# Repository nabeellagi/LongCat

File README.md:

<div align="center">

<!-- Zine -->

---

# Long Cat & FoxCharge

**A custom ESP32-C6 retro game console + fox-themed powerbank, built from scratch.**  
*By Nabeel — 18, Indonesia*

```
   /\_____/\
  /  o   o  \
 ( ==  ^  == )
```

</div>

---

## What Is This?

Long Cat is a handheld retro game console built around a custom ESP32-C6 PCB, put inside a 3D-printed enclosure featuring a long, stoopid cat on the back. It has a 1.3" OLED screen, 5 interface buttons, and a passive buzzer.

FoxCharge is its companion: a fox-themed powerbank with its own custom PCB, and a "Charging Social Battery" label on the back — totally relateable.

---

## Why Does This Exist?
The whole thing exists because I wanted a device where anyone could write their own retro-style game in firmware and actually play it on real hardware! A customizable silly looking project.

---

## How To Use It

### Coding & Flashing

This is the main loop. Open up Arduino IDE, write your game, and flash it to the console over USB-C.

1. Install [Arduino IDE](https://www.arduino.cc/en/software) and add ESP32 board support
2. Plug the console into your PC via USB-C
3. Open or write your game sketch
4. Select the correct board: **ESP32C6 Dev Module**
5. Hit upload, watch it flash, iterate :D

The enclosure pops open magnetically so you never need to unscrew anything to get to the board.

### Playing & Sharing

Once your game is ready and you want to take it somewhere — or just not be tethered to a laptop:

1. Plug the console into the **FoxCharge powerbank** via USB-C
2. The console powers up from the powerbank's 5V output
3. Hand it to a friend. Or play it yourself.

### Modifying the Hardware

Want to tweak the circuit? Change a pin assignment? Add something new? Here's where to go:

- **Console PCB** — open `PCB/board/board.kicad_pro` in [KiCad](https://www.kicad.org/). The schematic, layout, and production files are all in there.
- **FoxCharge PCB** — open `PCB/powerbank/powerbank.epro` in [EasyEDA](https://easyeda.com/). The Interactive BOM HTML (`PCB/powerbank/INTERACTIVE BOM/InteractiveBOM_PCB1_2026-5-30.html`) is very helpful for cross-referencing components on the board visually.

---

## Hardware Overview

### Console

The brain of Long Cat. Designed in KiCad, built around the ESP32-C6.

| Part | What it does |
|---|---|
| **ESP32-C6** | The microcontroller. RISC-V, Wi-Fi 6, BLE 5. Runs your game code. |
| **1.3" OLED** | The screen. I2C, connected on SDA/SCL. This is where everything gets drawn. |
| **5x Buttons** | `BTN_1` through `BTN_5` — your game inputs. Wired to dedicated GPIO pins. |
| **Passive Buzzer** | Makes noise. Driven by a transistor on `BUZZER_PIN`. Louder than what you'd expect!! |
| **Reset / Boot switches** | `SW1` = reset the board, `SW2` = enter bootloader. Useful during development. |
| **Debug header (J1)** | 6-pin header exposing EN, 3V3, TX, GND, RX, BOOT — for serial monitoring or alternate flashing setups. |

### FoxCharge Powerbank

The power source. Custom PCB designed in EasyEDA. Fox-themed. Sleeping fox on the front is load-bearing.

| Part | What it does |
|---|---|
| **Battery** | LiPo 103450 cell (~2000 mAh). |
| **Charge IC — TP4056** | Handles charging the LiPo safely from the USB-C input port. |
| **Boost IC — MT3608** | Steps up the battery voltage (~3.7V) to a stable 5V for the USB-C output. |
| **Protection IC — DW01A + FS8205A** | Protects the battery from overcharge, overdischarge, and short circuits. Keeps things from catching fire. |
| **USB-C Input** | Plug in a charger here to charge the battery. |
| **USB-C Output** | Plug the console here. This is what powers the game. |

---

## Assembly

### Long Cat Console

<p align="center">
  
  <br/>
  
  <br/>
  
</p>

The front and back halves of the enclosure are held together using **6 x 2mm neodymium magnets** on the edges. This means the case snaps shut cleanly and can be pulled apart for flashing or debugging without any tools — which matters a lot when you're iterating on your game code.

To secure the PCB inside the front half: use **M2 screws with nylon M2 nuts**. Nylon nuts ensures the PCB will be locked into the top of the enclosure. Full screw spec is in the BOM (`REAL_BOM/console.csv`).

The Long Cat sticker goes on the back and the Sleepy cat on the front. **This is not optional!!!**.

---

### FoxCharge Powerbank

<p align="center">
  
  <br/>
  
  <br/>
  
  <br/>
  
</p>

Inside the powerbank enclosure, the LiPo battery and PCB are separated using **padded EVA foam** to prevent contact, pressure damage, and general battery unhappiness.

On the inner edges, **Dual Lock Reclosable Fastener (24mm × 50cm Velcro-style)** is used to hold the assembly in place while still allowing it to be opened cleanly for battery replacement or inspection.

Same M2 screw + nylon nut approach as the console for securing the PCB. See `REAL_BOM/powerbank.csv` for the full list.

---

### PCB and Schematics Wiring

<p align="center">
  
  <br/>
  
  <br/>
  
  <br/>
  
  <br/>

</p>

---

## Repository Structure

```
.
├── PCB/
│   ├── board/                          # Console PCB (KiCad)
│   │   ├── board.kicad_pcb
│   │   ├── board.kicad_sch
│   │   ├── board.kicad_pro
│   │   ├── STEP/board.step
│   │   └── production/
│   │       ├── board_gerber.zip        # Send this to your fab
│   │       ├── netlist.ipc
│   │       ├── bom.csv-JLCPCB BOM Tool.xls
│   │       └── raw_bom.csv
│   └── powerbank/                      # FoxCharge PCB (EasyEDA)
│       ├── powerbank.epro
│       ├── powerbank_netlist.tel
│       ├── STEP/
│       ├── GERBER/powerbank_gerber.zip
│       └── INTERACTIVE BOM/
│           ├── BOM_Board1_PCB1_2026-05-30.xlsx
│           └── InteractiveBOM_PCB1_2026-5-30.html
├── enclosure/
│   ├── rawrenders/                     # Reference renders for assembly + zine
│   ├── console/
│   │   ├── enclosure_only.3mf          # Print this
│   │   ├── fullassemblyvisual.3mf      # Full assembly reference
│   │   └── fullassemblyvisual.step
│   └── powerbank/
│       ├── enclosure_only.3mf
│       ├── fullassemblyvisual.3mf
│       └── fullassemblyvisual.step
├── firmware/                           # Hello World for the console
├── stickers/
│   ├── longcat.png
│   ├── sleepcat.png
│   └── tiredfox.png
├── REAL_BOM/
│   ├── all.xlsx
│   ├── console.csv
│   ├── powerbank.csv
│   └── total.csv
└── zine/                               # Full project zine, PDF + PNG versions
```

---

## Stickers

Three stickers are included in `stickers/`. Print them on sticker paper and apply accordingly.

- `longcat.png` — The long, stoopid cat. Goes on the back of the console.
- `sleepcat.png` — Sleeping cat. Goes on the front of the console.
- `tiredfox.png` — The FoxCharge mascot. Goes on the powerbank.

---

## Zine

The `zine/` folder contains both a PDF and PNG version of the project zine, made for Fallout 2026. It's the fastest way to understand what this project is about.

---

## Firmware

An example given inside firmware folder. A simple mechanism to see OLED's output based on button presses. Use it as a starting point for your own games!

---

## OnShape Links
- [Check out the console enclosure](https://cad.onshape.com/documents/60f1f5947965f7d5a461c6ea/w/f31938c96fb582cd81c805fc/e/fdd6c70c168f7e2d293480c5?renderMode=0&uiState=6a1faab33bd1e6d24cdd9844)
- [Check out the powerbank enclosure](https://cad.onshape.com/documents/b2bd0c68b06dcbd9cb3796b5/w/1a262ecd5f3c2cdca41969fa/e/07a6aa8a28141834d2369848?renderMode=0&uiState=6a1faae954f1b396560d079b)

## Bill of Materials

Full BOM is split by subsystem for easier ordering, here are the BOM links:

| File | Contents |
|---|---|
| [`REAL_BOM/console.csv`](https://github.com/nabeellagi/LongCat/blob/main/REAL_BOM/console.csv) | All console PCB components |
| [`REAL_BOM/powerbank.csv`](https://github.com/nabeellagi/LongCat/blob/main/REAL_BOM/powerbank.csv) | All powerbank PCB components |
| [`REAL_BOM/all.xlsx`](https://github.com/nabeellagi/LongCat/blob/main/REAL_BOM/all.xlsx) | Combined, formatted |
| [`REAL_BOM/total.csv`](https://github.com/nabeellagi/LongCat/blob/main/REAL_BOM/total.csv) | Grand total cost summary |

Additional BOM:

1. `PCB/board/production/bom.csv-JLCPCB BOM Tool.xls` is JLCPCB-formatted, ready to upload
2. For the powerbank PCB, the Interactive BOM HTML (`PCB/powerbank/INTERACTIVE BOM/InteractiveBOM_PCB1_2026-5-30.html`) is the friendliest way to cross-reference components with their board placement.

---

### Console BOM

| # | Item | Description | Qty | Unit ($) | Total ($) | Running Total ($) | Link |
|---|---|---|---|---|---|---|---|
| 1 | ESPRESSIF ESP32-C6-WROOM-1-N8 | ESP32 Chip | 1 | 4.3546 | 4.3546 | 4.3546 | [LCSC](https://www.lcsc.com/product-detail/C5366877.html) |
| 2 | TECH PUBLIC TPESD9B3.3ST5G | Diode | 3 | 0.0396 | 0.1188 | 4.4734 | [LCSC](https://www.lcsc.com/product-detail/C2682285.html) |
| 3 | TECH PUBLIC USBLC6-2SC6 | Transient Voltage Suppressor | 1 | 0.0410 | 0.0410 | 4.5144 | [LCSC](https://www.lcsc.com/product-detail/C2827654.html) |
| 4 | BZCN TSC016A04518A | Tactile Switches (console buttons) | 5 | 0.0107 | 0.0535 | 4.5679 | [LCSC](https://www.lcsc.com/product-detail/C2888493.html) |
| 5 | TI LM1117MP-3.3 | Voltage Regulator | 1 | 0.2975 | 0.2975 | 4.8654 | [LCSC](https://www.lcsc.com/product-detail/C3750685.html) |
| 6 | XHXDZ 1207-P6.5MM | Buzzer | 1 | 0.0316 | 0.0316 | 4.8970 | [LCSC](https://www.lcsc.com/product-detail/C49246964.html) |
| 7 | 1N5817W | Diode Schottky | 1 | 0.0197 | 0.0197 | 4.9167 | [LCSC](https://www.lcsc.com/product-detail/C727113.html) |
| 8 | MMBT2222A | Bipolar Transistor | 1 | 0.0155 | 0.0155 | 4.9322 | [LCSC](https://www.lcsc.com/product-detail/C7420351.html) |
| 9 | HS HS13L03W2C01 | 1.3" OLED | 1 | 5.3558 | 5.3558 | 10.2880 | [LCSC](https://www.lcsc.com/product-detail/C7465997.html) |
| 10 | muRata BLM21PG220SN1D | Ferrite Bead | 1 | 0.0308 | 0.0308 | 10.3188 | [LCSC](https://www.lcsc.com/product-detail/C88993.html) |
| 11 | Resistor 1kΩ | R6 | 1 | 0.0011 | 0.0011 | 10.3199 | [LCSC](https://www.lcsc.com/product-detail/C11702.html) |
| 12 | Capacitor 100nF | C2, C5 | 2 | 0.0016 | 0.0032 | 10.3231 | [LCSC](https://www.lcsc.com/product-detail/C1525.html) |
| 13 | Capacitor 1uF | C3, C4 | 2 | 0.0098 | 0.0196 | 10.3427 | [LCSC](https://www.lcsc.com/product-detail/C15849.html) |
| 14 | Korean Hroparts Elec TYPE-C-31-M-12 | USB-C Input | 1 | 0.1725 | 0.1725 | 10.5152 | [LCSC](https://www.lcsc.com/product-detail/C165948.html) |
| 15 | Capacitor 10uF | C1 | 1 | 0.2500 | 0.2500 | 10.7652 | [LCSC](https://www.lcsc.com/product-detail/C19702.html) |
| 16 | B3U-1000P | ESP32 Buttons | 3 | 0.1781 | 0.5343 | 11.2995 | [LCSC](https://www.lcsc.com/product-detail/C231329.html) |
| 17 | Resistor 2.2kΩ | R7, R8 | 2 | 0.0008 | 0.0008 | 11.3003 | [LCSC](https://www.lcsc.com/product-detail/C25879.html) |
| 18 | Resistor 5.1kΩ | R4, R5 | 2 | 0.0009 | 0.0018 | 11.3021 | [LCSC](https://www.lcsc.com/product-detail/C25905.html) |
| 19 | Capacitor 22uF | C6, C7 | 2 | 0.0618 | 0.1236 | 11.4257 | [LCSC](https://www.lcsc.com/product-detail/C45783.html) |
| 20 | R+O SMD1206-050-30 | Reset Fuse | 1 | 0.0599 | 0.0599 | 11.4856 | [LCSC](https://www.lcsc.com/product-detail/C46641016.html) |
| 21 | ZHOURI 2.54-2*3 | Pin Header | 1 | 0.0562 | 0.0562 | 11.5418 | [LCSC](https://www.lcsc.com/product-detail/C5116479.html) |
| 22 | Resistor 10kΩ | R1, R2, R3 | 3 | 0.0009 | 0.0027 | 11.5445 | [LCSC](https://www.lcsc.com/product-detail/C60490.html) |
| 23 | 6×2mm Strong Magnet Neodymium | Enclosure attach/detach | 6 | 0.0530 | 0.3180 | 11.8625 | [Tokopedia](https://tk.tokopedia.com/ZSxcDM12f/) |
| 24 | M2×8 Screw | Screw PCB to enclosure | 4 | 0.0500 | 0.2000 | 12.0625 | [Tokopedia](https://tk.tokopedia.com/ZSxcDKrx9/) |
| 25 | M2 Nylon Nut | Lock the screw | 4 | 0.0540 | 0.2160 | 12.2785 | [Tokopedia](https://tk.tokopedia.com/ZSxcP4PVw/) |
| 26 | Engineering Fee | Engineering Fee | 1 | 24.0000 | 24.0000 | 36.2785 | [JLCPCB](https://jlcpcb.com/) |
| 27 | PCB Board | PCB Board | 1 | 1.6000 | 1.6000 | 37.8785 | [JLCPCB](https://jlcpcb.com/) |
| 28 | PCBA Price | If enabled PCBA option | 1 | 42.1700 | 42.1700 | 80.0485 | [JLCPCB](https://jlcpcb.com/) |

> **Console subtotal (without PCBA): $37.88** — components + engineering fee + PCB board  
> **Console subtotal (with PCBA): $80.05** — includes assembly service

---

### FoxCharge Powerbank BOM

| # | Item | Description | Qty | Unit ($) | Total ($) | Running Total ($) | Link |
|---|---|---|---|---|---|---|---|
| 1 | TPOWER TP4056 | Charging Module | 1 | 0.1194 | 0.1194 | 0.1194 | [LCSC](https://www.lcsc.com/product-detail/C382139.html) |
| 2 | PUOLOP DW01A | Battery Protection (overcharge prevention) | 1 | 0.0428 | 0.0428 | 0.1622 | [LCSC](https://www.lcsc.com/product-detail/C351410.html) |
| 3 | XI'AN Aerosemi Tech MT3608 | Boost Step-Up Regulator | 1 | 0.0786 | 0.0786 | 0.2408 | [LCSC](https://www.lcsc.com/product-detail/C84817.html) |
| 4 | TECH PUBLIC FS8205A | LiPo Battery Protection FET | 1 | 0.0575 | 0.0575 | 0.2983 | [LCSC](https://www.lcsc.com/product-detail/C2830320.html) |
| 5 | SHOU HAN TYPE-C 16PIN 2MD(073) | USB-C Input and Output | 2 | 0.0742 | 0.1484 | 0.4467 | [LCSC](https://www.lcsc.com/product-detail/C2765186.html) |
| 6 | Hubei KENTO Elec KT-0603R | Red LED | 1 | 0.0070 | 0.0070 | 0.4537 | [LCSC](https://www.lcsc.com/product-detail/C2286.html) |
| 7 | Hubei KENTO Elec KT-0805G | Green LED | 1 | 0.0163 | 0.0163 | 0.4700 | [LCSC](https://www.lcsc.com/product-detail/C2297.html) |
| 8 | EVERLIGHT 19-213/BHC-ZL1M2RY/5T | Blue LED | 1 | 0.0381 | 0.0381 | 0.5081 | [LCSC](https://www.lcsc.com/product-detail/C2987539.html) |
| 9 | cjiang FXL0420-4R7-M | Inductor 4.7µH | 1 | 0.2076 | 0.2076 | 0.7157 | [LCSC](https://www.lcsc.com/product-detail/C167208.html) |
| 10 | JST S2B-PH-SM4-TB(LF)(SN) | JST Pin for Battery | 1 | 0.2040 | 0.2040 | 0.9197 | [LCSC](https://www.lcsc.com/product-detail/C295747.html) |
| 11 | LiPo 104050 2000mAh 3.7V | Battery | 1 | 4.8300 | 4.8300 | 5.7497 | [Tokopedia](https://tk.tokopedia.com/ZSxtYCQTL/) |
| 12 | Resistor 5.1kΩ | R1, R2 | 2 | 0.0003 | 0.0006 | 5.7503 | [LCSC](https://www.lcsc.com/product-detail/C23186.html) |
| 13 | Resistor 470Ω | R3, R4 | 2 | 0.0003 | 0.0006 | 5.7509 | [LCSC](https://www.lcsc.com/product-detail/C23179.html) |
| 14 | Resistor 10kΩ | R5 | 1 | 0.0003 | 0.0003 | 5.7512 | [LCSC](https://www.lcsc.com/product-detail/C25804.html) |
| 15 | Resistor 1.2kΩ | R6 | 1 | 0.0003 | 0.0003 | 5.7515 | [LCSC](https://www.lcsc.com/product-detail/C114605.html) |
| 16 | Resistor 1kΩ | R7, R12 | 2 | 0.0003 | 0.0006 | 5.7521 | [LCSC](https://www.lcsc.com/product-detail/C22548.html) |
| 17 | Resistor 110kΩ | R8 | 1 | 0.0002 | 0.0002 | 5.7523 | [LCSC](https://www.lcsc.com/product-detail/C25805.html) |
| 18 | Resistor 15kΩ | R9 | 1 | 0.0003 | 0.0003 | 5.7526 | [LCSC](https://www.lcsc.com/product-detail/C114661.html) |
| 19 | Resistor 56kΩ | R10, R11 | 2 | 0.0003 | 0.0006 | 5.7532 | [LCSC](https://www.lcsc.com/product-detail/C23206.html) |
| 20 | Resistor 100Ω | R13 | 1 | 0.0003 | 0.0003 | 5.7535 | [LCSC](https://www.lcsc.com/product-detail/C105588.html) |
| 21 | Capacitor 10uF | C1, C2 | 2 | 0.0019 | 0.0038 | 5.7573 | [LCSC](https://www.lcsc.com/product-detail/C19702.html) |
| 22 | Capacitor 22uF | C3, C4 | 2 | 0.0027 | 0.0054 | 5.7627 | [LCSC](https://www.lcsc.com/product-detail/C86295.html) |
| 23 | Capacitor 100nF | C6 | 1 | 0.0003 | 0.0003 | 5.7630 | [LCSC](https://www.lcsc.com/product-detail/C160831.html) |
| 24 | 3M Dual Lock Fastener 24mm×50cm | Enclosure attach/detach (use 3mm×3mm pieces) | 6 | 0.0010 | 0.0060 | 5.7690 | [Tokopedia](https://tk.tokopedia.com/ZSxcDnUcT/) |
| 25 | M2×8 Screw | Screw PCB to enclosure | 4 | 0.0500 | 0.2000 | 5.9690 | [Tokopedia](https://tk.tokopedia.com/ZSxcDKrx9/) |
| 26 | M2 Nylon Nut | Lock the screw | 4 | 0.0540 | 0.2160 | 6.1850 | [Tokopedia](https://tk.tokopedia.com/ZSxc5xuDv/) |
| 27 | PCB Board | PCB Board | 1 | 1.0000 | 1.0000 | 7.1850 | [JLCPCB](https://jlcpcb.com/) |
| 28 | PCBA Price | If enabled PCBA option | 1 | 70.2500 | 70.2500 | 77.4350 | [JLCPCB](https://jlcpcb.com/) |

> **Powerbank subtotal (without PCBA): $7.19** — components + PCB board  
> **Powerbank subtotal (with PCBA): $77.44** — includes assembly service

---

### Grand Total

| Scenario | Console | Powerbank | **Total** |
|---|---|---|---|
| **Without PCBA** (self-solder) | $37.88 | $7.19 | **$45.06** |
| **With PCBA** (JLCPCB assembles) | $80.05 | $77.44 | **$157.48** |

> PCBA (PCB Assembly) is the option where JLCPCB solders all SMD components onto the board for you.

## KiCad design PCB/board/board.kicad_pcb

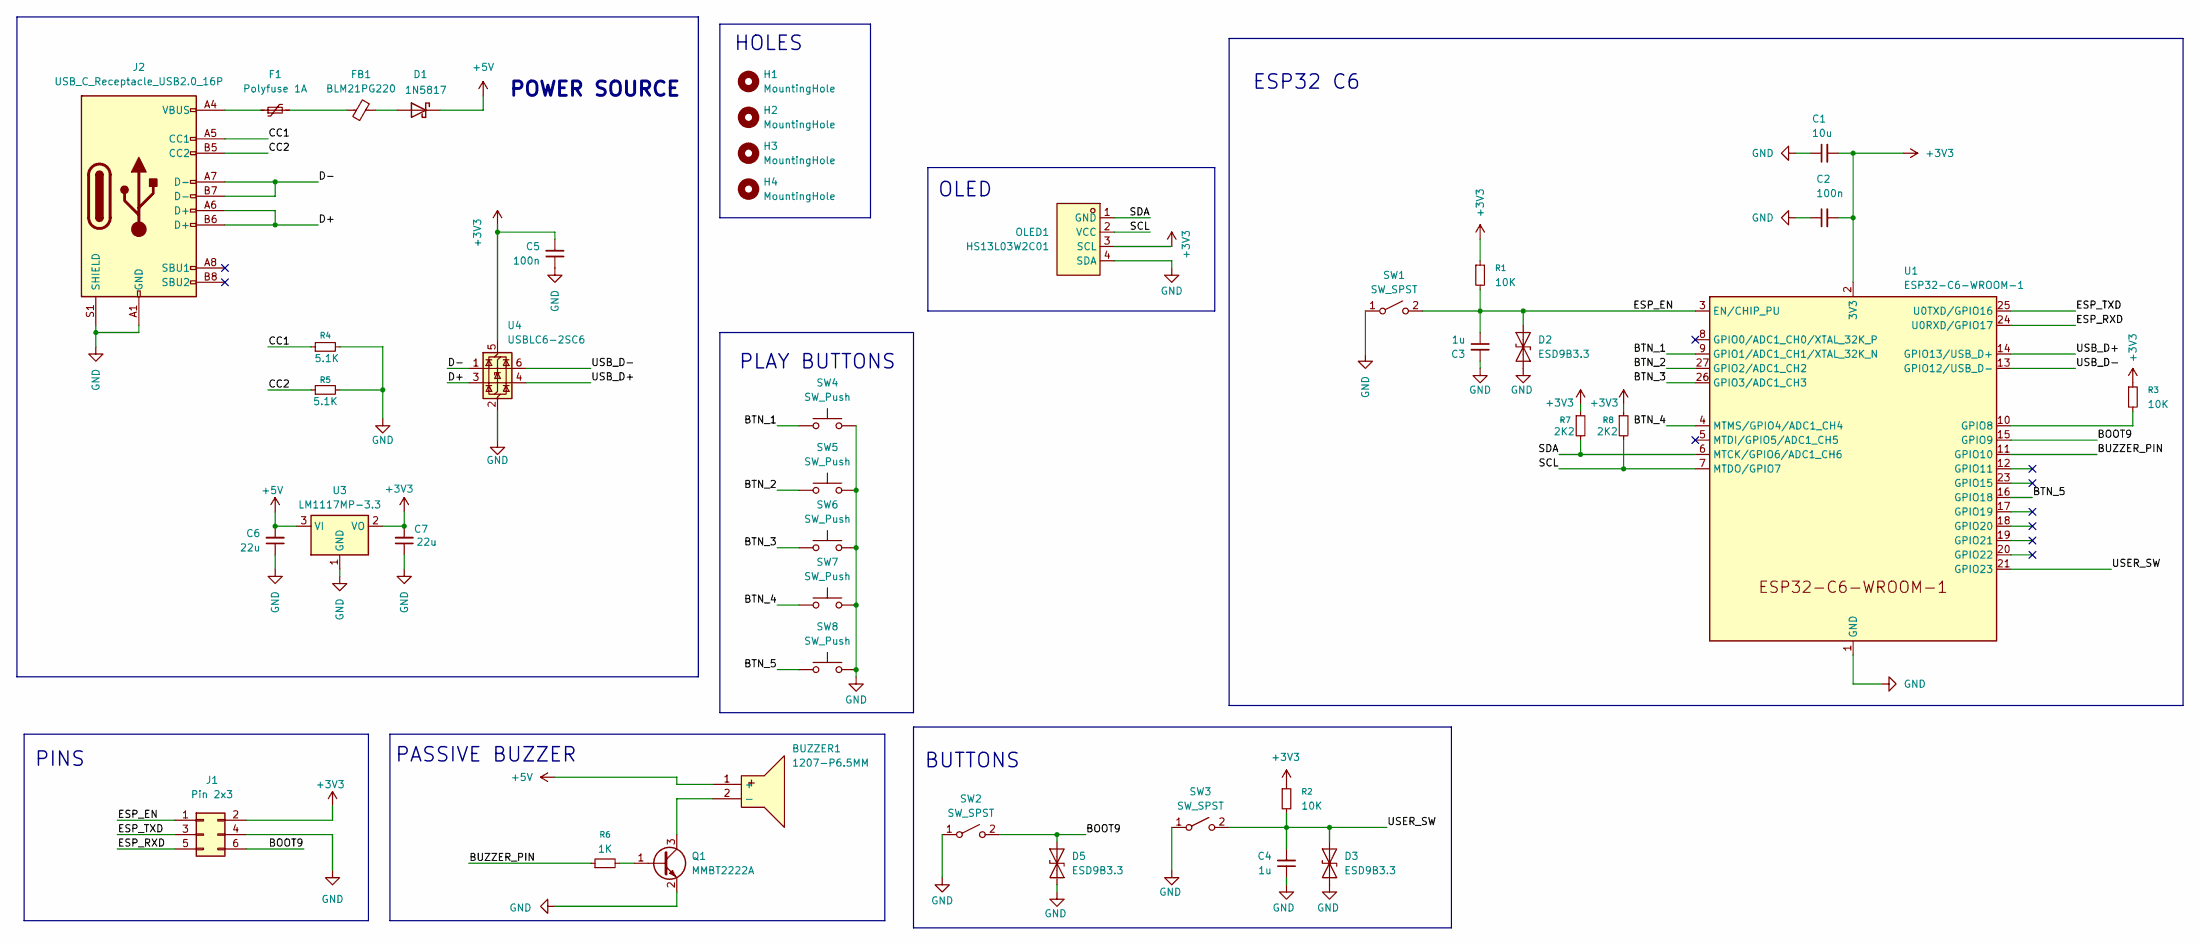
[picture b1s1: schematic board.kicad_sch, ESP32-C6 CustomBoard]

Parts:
BUZZER1: 1207-P6.5MM; BUZ-TH_BD12.5-P6.50-D1.4; MPN 1207-P6.5MM; LCSC Part C49246964
C1: 10u; C_0603_1608Metric
C2, C5: 100n; C_0402_1005Metric
C3, C4: 1u; C_0603_1608Metric
C6, C7: 22u; C_0805_2012Metric
D1: 1N5817; D_SOD-123
D2, D3, D5: ESD9B3.3; D_SOD-923
F1: Polyfuse 1A; Fuse_1206_3216Metric
FB1: BLM21PG220; L_0805_2012Metric
H1, H2, H3, H4: MountingHole; MountingHole_2.2mm_M2_DIN965_Pad
J1: Pin 2x3; PinSocket_2x03_P2.54mm_Vertical
J2: USB_C_Receptacle_USB2.0_16P; USB_C_Receptacle_HRO_TYPE-C-31-M-12
OLED1: HS13L03W2C01; OLED-TH_L35.4-W33.5_HS13L03W2C01; MPN HS13L03W2C01; LCSC Part C7465997
Q1: MMBT2222A; SOT-23
R1, R2, R3: 10K; R_0402_1005Metric
R4, R5: 5.1K; R_0402_1005Metric
R6: 1K; R_0402_1005Metric
R7, R8: 2K2; R_0402_1005Metric
SW1, SW2, SW3: SW_SPST; SW_SPST_B3U-1000P
SW4, SW5, SW6, SW7, SW8: SW_Push; SW-TH_4P-L4.5-W4.5-P3.00-LS4.8
U1: ESP32-C6-WROOM-1
U3: LM1117MP-3.3; SOT-223-3_TabPin2
U4: USBLC6-2SC6; SOT-23-6

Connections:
+3V3: C1.2, C2.2, C5.2, C7.2, J1.2, OLED1.3 (SCL), R1.1, R2.1, R3.1, R7.1, R8.1, U1.2 (3V3), U3.2 (VO), U4.5 (VBUS)
+5V: BUZZER1.1 (+), C6.2, D1.1 (K), U3.3 (VI)
/BOOT9: D5.2 (A2), J1.6, SW2.2 (B), U1.15 (GPIO9)
/BTN_1: SW4.2, U1.9 (GPIO1/ADC1_CH1/XTAL_32K_N)
/BTN_2: SW5.2, U1.27 (GPIO2/ADC1_CH2)
/BTN_3: SW6.2, U1.26 (GPIO3/ADC1_CH3)
/BTN_4: SW7.2, U1.4 (MTMS/GPIO4/ADC1_CH4)
/BTN_5: SW8.2, U1.16 (GPIO18)
/BUZZER_PIN: R6.1, U1.11 (GPIO10)
/CC1: J2.A5 (CC1), R4.1
/CC2: J2.B5 (CC2), R5.1
/D+: J2.A6 (D+), J2.B6 (D+), U4.3 (I/O2)
/D-: J2.A7 (D-), J2.B7 (D-), U4.1 (I/O1)
/ESP_EN: C3.1, D2.2 (A2), J1.1, R1.2, SW1.2 (B), U1.3 (EN/CHIP_PU)
/ESP_RXD: J1.5, U1.24 (U0RXD/GPIO17)
/ESP_TXD: J1.3, U1.25 (U0TXD/GPIO16)
/SCL: OLED1.2 (VCC), R8.2, U1.7 (MTDO/GPIO7)
/SDA: OLED1.1 (GND), R7.2, U1.6 (MTCK/GPIO6/ADC1_CH6)
/USB_D+: U1.14 (GPIO13/USB_D+), U4.4 (I/O2)
/USB_D-: U1.13 (GPIO12/USB_D-), U4.6 (I/O1)
/USER_SW: C4.2, D3.2 (A2), R2.2, SW3.2 (B), U1.21 (GPIO23)
GND: C1.1, C2.1, C3.2, C4.1, C5.1, C6.1, C7.1, D2.1 (A1), D3.1 (A1), D5.1 (A1), J1.4, J2.A1 (GND), J2.A12 (GND), J2.B1 (GND), J2.B12 (GND), J2.S1 (SHIELD), OLED1.4 (SDA), Q1.2 (E), R4.2, R5.2, SW1.1 (A), SW2.1 (A), SW3.1 (A), SW4.1, SW5.1, SW6.1, SW7.1, SW8.1, U1.1 (GND), U1.28 (GND), U1.29 (GND), U3.1 (GND), U4.2 (GND)
unnamed: BUZZER1.2 (-), Q1.3 (C)
unnamed: D1.2 (A), FB1.2
unnamed: F1.1, J2.A4 (VBUS), J2.A9 (VBUS), J2.B4 (VBUS), J2.B9 (VBUS)
unnamed: F1.2, FB1.1
unnamed: Q1.1 (B), R6.2
unnamed: R3.2, U1.10 (GPIO8)

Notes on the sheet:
PINS
OLED
PASSIVE BUZZER
PLAY BUTTONS
HOLES
ESP32 C6
BUTTONS
POWER SOURCE

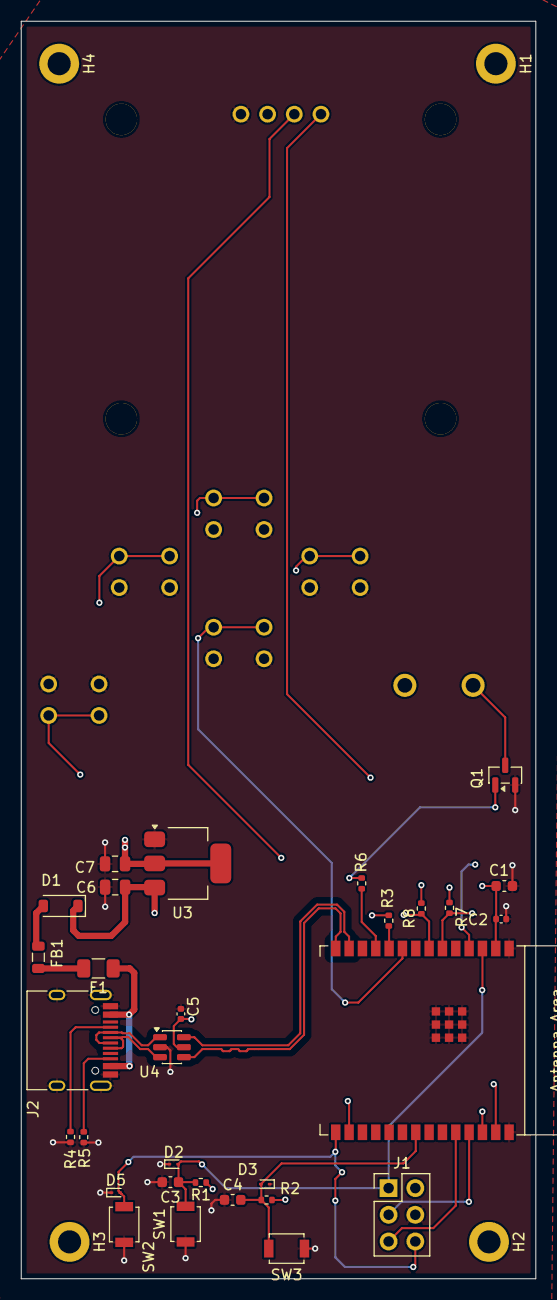
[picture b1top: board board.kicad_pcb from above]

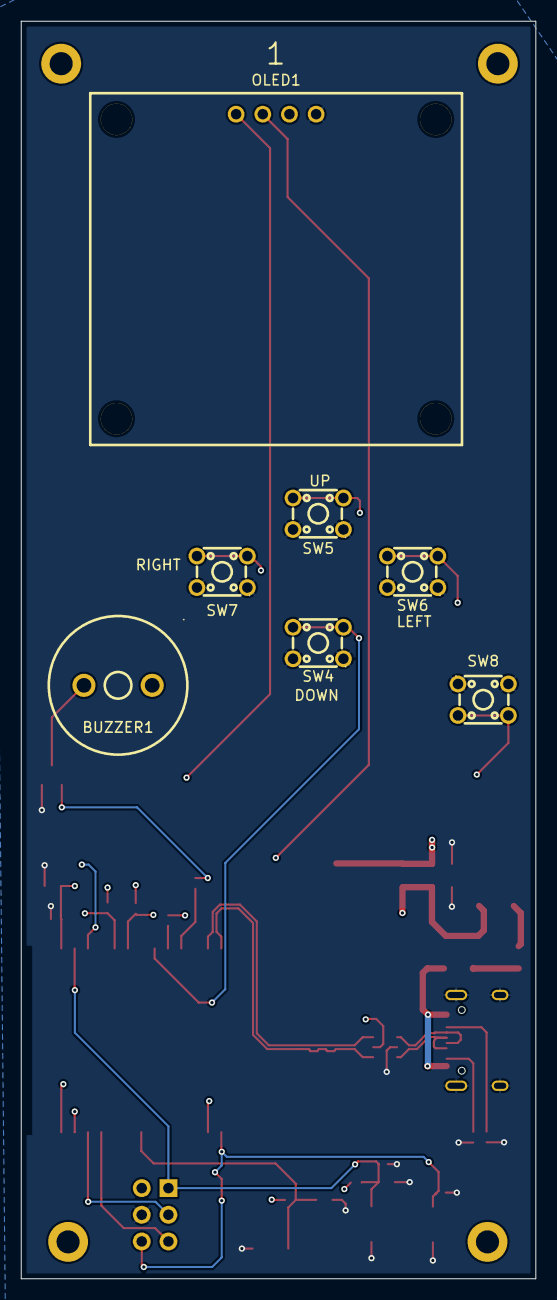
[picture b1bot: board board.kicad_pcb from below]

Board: 4 copper layers, 49.0 x 119.8 mm, 41 parts (7 on the bottom side), 28 nets.

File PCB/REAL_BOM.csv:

Number,Item,Description,Quantity,Unit Price ($),Total Price ($),URL,Running Total ($ with Tax)
1,ESPRESSIF ESP32-C6-WROOM-1-N8,ESP32 Chip,1,4.3546,4.3546,https://www.lcsc.com/product-detail/C5366877.html,4.3546
2,TECH PUBLIC TPESD9B3.3ST5G,Diode,3,0.0396,0.1188,https://www.lcsc.com/product-detail/C2682285.html,4.4734
3,TECH PUBLIC USBLC6-2SC6,Transient Voltage Supressor,1,0.041,0.041,https://www.lcsc.com/product-detail/C2827654.html,4.5144
4,BZCN TSC016A04518A,Tactile Switches for console button,5,0.0107,0.0535,https://www.lcsc.com/product-detail/C2888493.html,4.5679
5,TI LM1117MP-3.3,Voltage Regulators,1,0.2975,0.2975,https://www.lcsc.com/product-detail/C3750685.html,4.8654
6,XHXDZ 1207-P6.5MM,Buzzer,1,0.0316,0.0316,https://www.lcsc.com/product-detail/C49246964.html,4.897
7,1N5817W,DIODE SCHOTTKY,1,0.0197,0.0197,https://www.lcsc.com/product-detail/C727113.html,4.9167
8,MMBT2222A,Bipolar Transistor,1,0.0155,0.0155,https://www.lcsc.com/product-detail/C7420351.html,4.9322
9,HS HS13L03W2C01,"1.3"" OLED",1,5.3558,5.3558,https://www.lcsc.com/product-detail/C7465997.html,10.288
10,muRata BLM21PG220SN1D,Ferrite Beads and Chips,1,0.0308,0.0308,https://www.lcsc.com/product-detail/C88993.html,10.3188
11,Resistor 1kΩ,R6,1,0.0011,0.0011,https://www.lcsc.com/product-detail/C11702.html,10.3199
12,Capacitor 100nF,"C2, C5",2,0.0016,0.0032,https://www.lcsc.com/product-detail/C1525.html,10.3231
13,Capacitor 1uF,"C3, C4",2,0.0098,0.0196,https://www.lcsc.com/product-detail/C15849.html,10.3427
14,Korean Hroparts Elec TYPE-C-31-M-12,USB C Input,1,0.1725,0.1725,https://www.lcsc.com/product-detail/C165948.html,10.5152
15,Capacitor 10uF,C1,1,0.25,0.25,https://www.lcsc.com/product-detail/C19702.html,10.7652
16,B3U-1000P,ESP32 buttons,3,0.1781,0.5343,https://www.lcsc.com/product-detail/C231329.html,11.2995
17,Resistor 2.2kΩ,"R7, R8",2,0.0008,0.0008,https://www.lcsc.com/product-detail/C25879.html,11.3003
18,Resistor 5.1kΩ,"R4, R5",2,0.0009,0.0018,https://www.lcsc.com/product-detail/C25905.html,11.3021
19,Capacitor 22uF,"C6, C7",2,0.0618,0.1236,https://www.lcsc.com/product-detail/C45783.html,11.4257
20,R+O SMD1206-050-30,Reset Fuse,1,0.0599,0.0599,https://www.lcsc.com/product-detail/C46641016.html,11.4856
21,ZHOURI 2.54-2*3,Pin Header,1,0.0562,0.0562,https://www.lcsc.com/product-detail/C5116479.html,11.5418
22,Resistor 10kΩ,"R1,R2,R3",3,0.0009,0.0027,https://www.lcsc.com/product-detail/C60490.html,11.5445

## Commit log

2026-06-03 Adding Firmware, BOM modification and Enclosure modification. Added README and Zine
2026-06-03 Changed README
2026-06-03 Added BOM links
2026-06-03 Added combined BOM
2026-06-03 Added combined BOM and renamed folder
2026-06-03 Added schematic and PCB screenshots
2026-06-08 Added engineering fee, board price, and PCBA service to the BOM.. Updated BOM and README (now Readme also have running total)
